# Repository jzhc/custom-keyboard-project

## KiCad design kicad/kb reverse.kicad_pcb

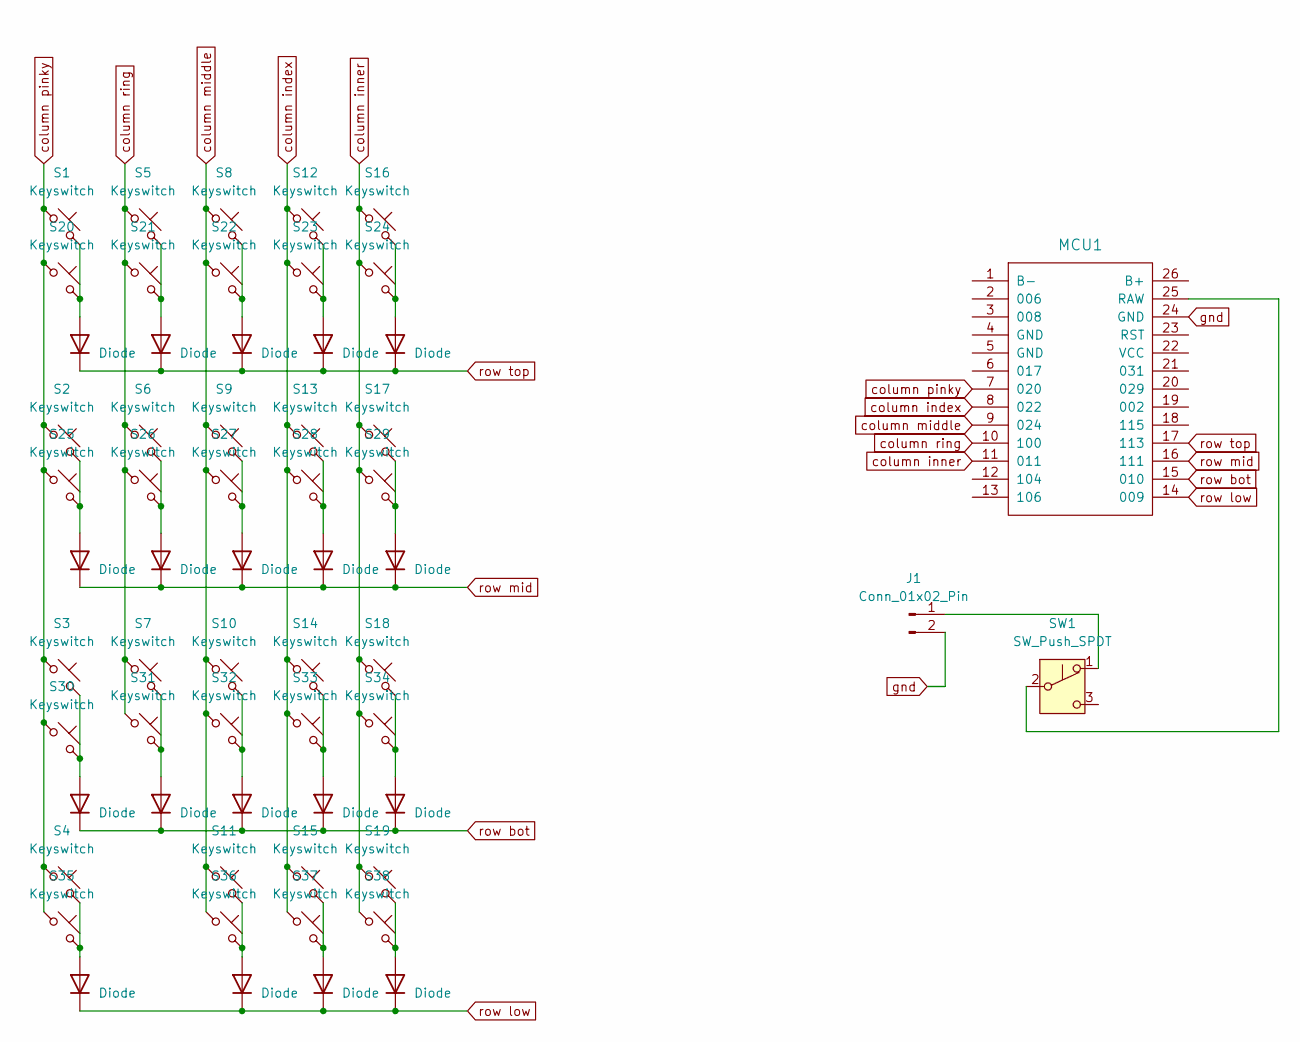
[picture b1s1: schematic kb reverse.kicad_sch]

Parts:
D1, D2, D3, D4, D5, D6, D7, D8, D9, D10, D11, D12, D13, D14, D15, D16, D17, D18, D19: Diode; SOD 323 DIODE USE THIS ONE
J1: Conn_01x02_Pin; JST_PH_B2B-PH-K_1x02_P2.00mm_Vertical
MCU1: PRO MICRO NRF; PROMICRO NRF52840
S1, S2, S3, S4, S5, S6, S7, S8, S9, S10, S11, S12, S13, S14, S15, S16, S17, S18, S19, S20, S21, S22, S23, S24, S25, S26, S27, S28, S29, S30, S31, S32, S33, S34, S35, S36, S37, S38: Keyswitch; GATERON SINGLE ORIGINAL
SW1: SW_Push_SPDT; SW_SPDT_PCM12

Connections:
unnamed: D1.2 (A), S1.2, S20.2
unnamed: D2.2 (A), S2.2, S25.2
unnamed: D3.2 (A), S3.2, S30.2
unnamed: D4.2 (A), S4.2, S35.2
unnamed: D5.2 (A), S5.2, S21.2
unnamed: D6.2 (A), S6.2, S26.2
unnamed: D7.2 (A), S7.2, S31.2
unnamed: D8.2 (A), S8.2, S22.2
unnamed: D9.2 (A), S9.2, S27.2
unnamed: D10.2 (A), S10.2, S32.2
unnamed: D11.2 (A), S11.2, S36.2
unnamed: D12.2 (A), S12.2, S23.2
unnamed: D13.2 (A), S13.2, S28.2
unnamed: D14.2 (A), S14.2, S33.2
unnamed: D15.2 (A), S15.2, S37.2
unnamed: D16.2 (A), S16.2, S24.2
unnamed: D17.2 (A), S17.2, S29.2
unnamed: D18.2 (A), S18.2, S34.2
unnamed: D19.2 (A), S19.2, S38.2
unnamed: J1.1, SW1.1 (A)
unnamed: MCU1.25 (RAW), SW1.2 (B)
column middle: MCU1.9 (024), S8.1, S9.1, S10.1, S11.1, S22.1, S27.1, S32.1, S36.1
column ring: MCU1.10 (100), S5.1, S6.1, S7.1, S21.1, S26.1, S31.1
column index: MCU1.8 (022), S12.1, S13.1, S14.1, S15.1, S23.1, S28.1, S33.1, S37.1
column inner: MCU1.11, S16.1, S17.1, S18.1, S19.1, S24.1, S29.1, S34.1, S38.1
column pinky: MCU1.7 (020), S1.1, S2.1, S3.1, S4.1, S20.1, S25.1, S30.1, S35.1
gnd: J1.2, MCU1.24 (GND)
row bot: D3.1 (K), D7.1 (K), D10.1 (K), D14.1 (K), D18.1 (K), MCU1.15 (010)
row low: D4.1 (K), D11.1 (K), D15.1 (K), D19.1 (K), MCU1.14 (009)
row mid: D2.1 (K), D6.1 (K), D9.1 (K), D13.1 (K), D17.1 (K), MCU1.16 (111)
row top: D1.1 (K), D5.1 (K), D8.1 (K), D12.1 (K), D16.1 (K), MCU1.17 (113)

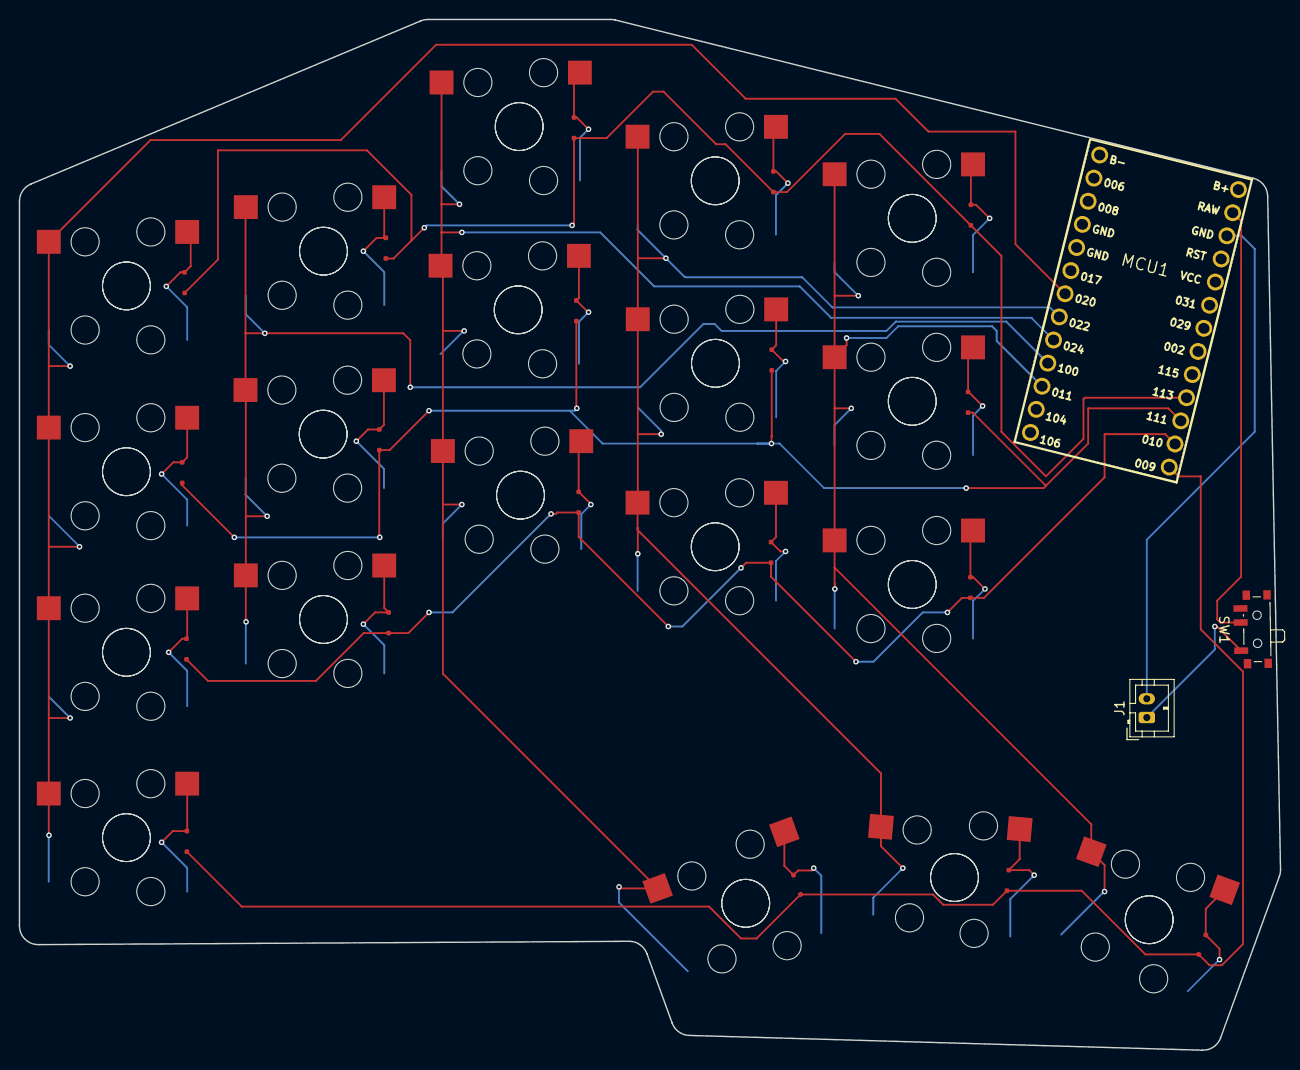
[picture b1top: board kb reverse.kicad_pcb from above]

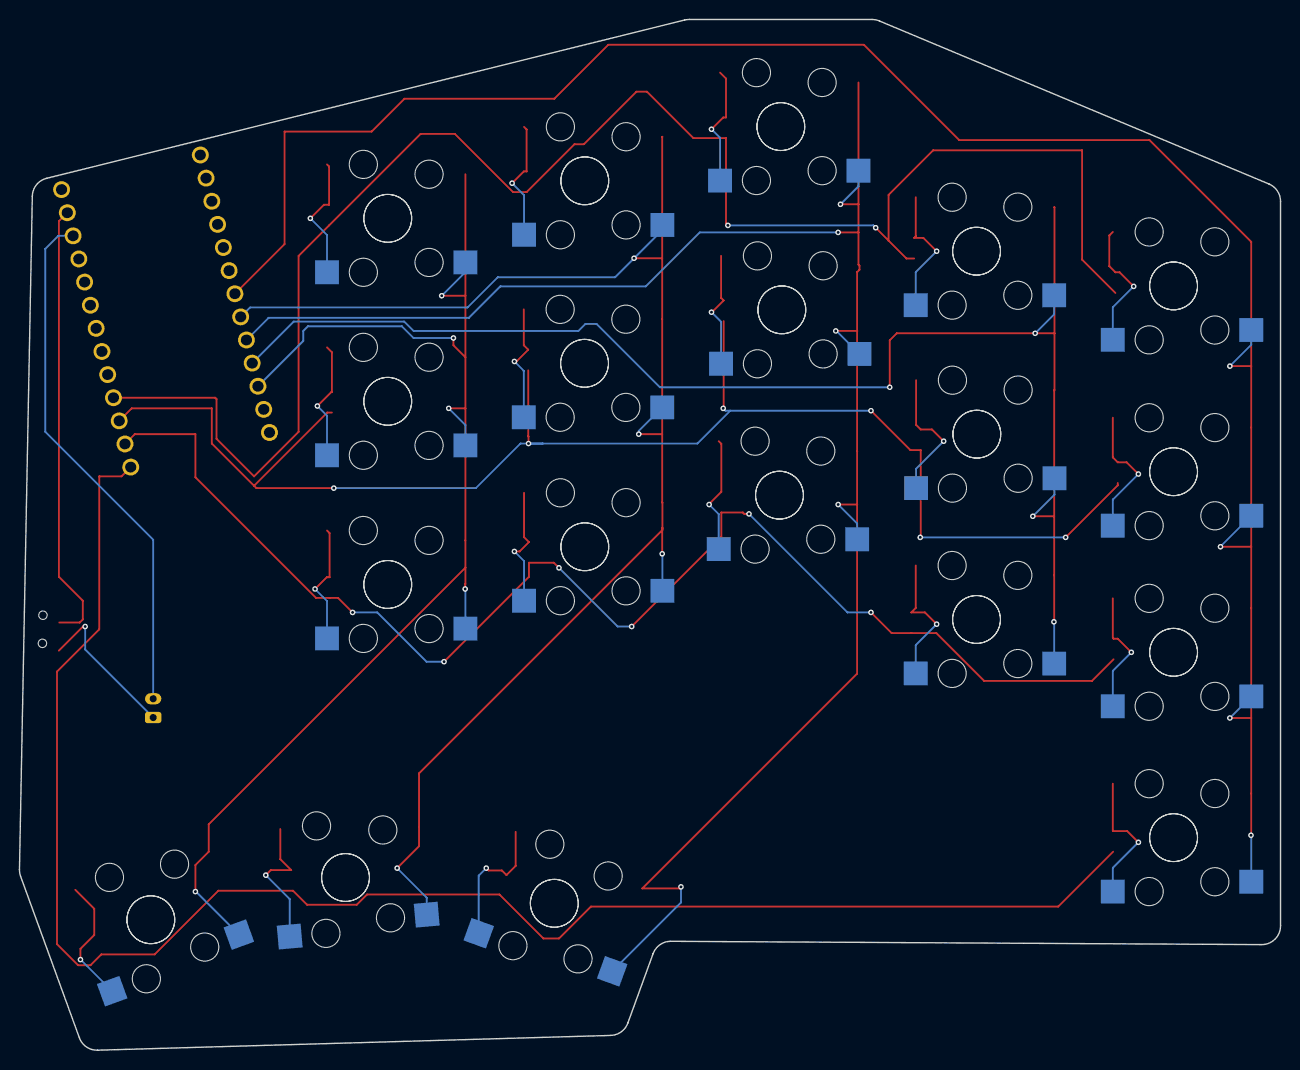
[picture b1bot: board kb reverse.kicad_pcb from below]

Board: 2 copper layers, 134.4 x 109.9 mm, 60 parts (19 on the bottom side), 31 nets.

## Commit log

2025-01-27 Create e
